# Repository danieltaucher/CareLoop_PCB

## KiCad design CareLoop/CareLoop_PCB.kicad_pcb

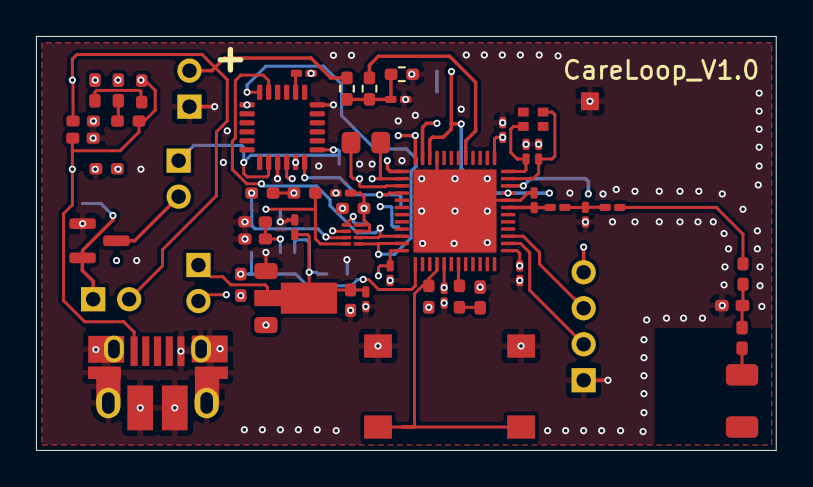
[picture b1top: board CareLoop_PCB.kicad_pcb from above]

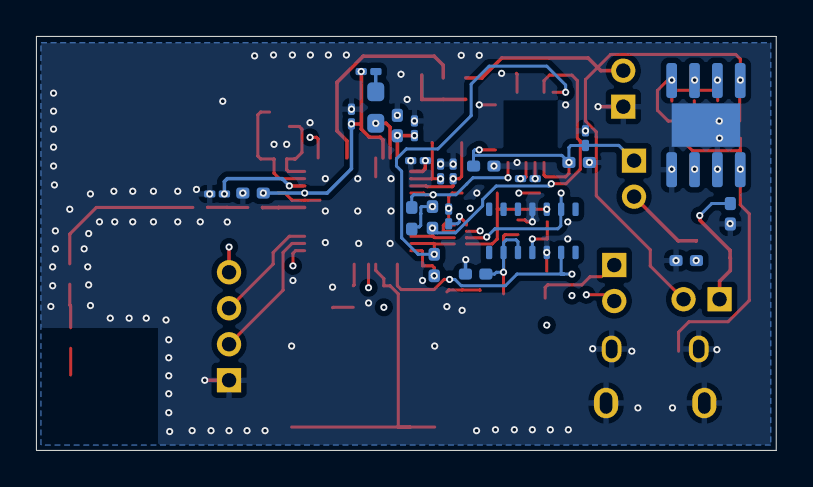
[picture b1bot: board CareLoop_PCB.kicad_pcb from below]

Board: 6 copper layers, 41.1 x 23.0 mm, 76 parts (23 on the bottom side), 43 nets.

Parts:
AE1: Antenna_Chip; Johanson_2450AT18x100
C1, C2: 12p; C_0201_0603Metric_Pad0.64x0.40mm_HandSolder
C3, C4: 4p; C_0201_0603Metric_Pad0.64x0.40mm_HandSolder
C5: 1p; C_0201_0603Metric_Pad0.64x0.40mm_HandSolder
C6: 1.2p; C_0201_0603Metric_Pad0.64x0.40mm_HandSolder
C7, C11, C22, C40, C42, C43: 1u; C_0402_1005Metric_Pad0.74x0.62mm_HandSolder
C8: 47n; C_0201_0603Metric_Pad0.64x0.40mm_HandSolder
C9, C26: 100p; C_0201_0603Metric_Pad0.64x0.40mm_HandSolder
C10, C12, C13, C13#2, C14, C15, C16, C20, C25, C27, C31, C32: 100n; C_0201_0603Metric_Pad0.64x0.40mm_HandSolder
C21, C23: 4.7u; C_0402_1005Metric_Pad0.74x0.62mm_HandSolder
C24, C41: 10u; C_0402_1005Metric_Pad0.74x0.62mm_HandSolder
C30, C30#2: 10n; C_0402_1005Metric_Pad0.74x0.62mm_HandSolder
C33: 2.2n; C_0201_0603Metric_Pad0.64x0.40mm_HandSolder
C50: C_Small; C_0402_1005Metric_Pad0.74x0.62mm_HandSolder
D3: LED_Small; LED_0402_1005Metric_Pad0.77x0.64mm_HandSolder
D40, D41: LED; LED_0402_1005Metric_Pad0.77x0.64mm_HandSolder
J1_Battery1: Conn_01x02_Pin; PinHeader_1x02_P2.00mm_Vertical
J1_DEBUG1: Conn_01x04_Pin; PinHeader_1x04_P2.00mm_Vertical
J2: USB_B_Micro; USB_Micro-B_Amphenol_10103594-0001LF_Horizontal
JP1_MAX30102, JP2_MPU1, JP2_MPU2: Jumper_2_Bridged; PinHeader_1x02_P2.00mm_Vertical
L1: 2.2n; L_0201_0603Metric_Pad0.64x0.40mm_HandSolder
L2: 4.7n; L_0201_0603Metric_Pad0.64x0.40mm_HandSolder
L5: 10u; L_0603_1608Metric_Pad1.05x0.95mm_HandSolder
L6: 15n; L_0201_0603Metric_Pad0.64x0.40mm_HandSolder
L50, L51: L_Small; L_0402_1005Metric_Pad0.77x0.64mm_HandSolder
R1, R20: 10k; R_0402_1005Metric_Pad0.72x0.64mm_HandSolder
R2, R3, R5, R22, R23: 4k7; R_0402_1005Metric_Pad0.72x0.64mm_HandSolder
R4: 800; R_0402_1005Metric_Pad0.72x0.64mm_HandSolder
R21: 200k; R_0402_1005Metric_Pad0.72x0.64mm_HandSolder
R40, R41: 1k; R_0402_1005Metric_Pad0.72x0.64mm_HandSolder
R42: 20k; R_0402_1005Metric_Pad0.72x0.64mm_HandSolder
R43: 120k; R_0402_1005Metric_Pad0.72x0.64mm_HandSolder
R44: 100; R_0402_1005Metric_Pad0.72x0.64mm_HandSolder
R45: 300k; R_0402_1005Metric_Pad0.72x0.64mm_HandSolder
Reset_SW1: SW_Push; SW_SPST_B3S-1000
U1: MCP1700x-180xxMB; SOT-89-3
U2: MAX30102; Maxim_OLGA-14_3.3x5.6mm_P0.8mm
U3: MPU-6050; InvenSense_QFN-24_4x4mm_P0.5mm
U4: MCP1700x-330xxMB; SOT-23
U5: TP4056-42-ESOP8; SOIC-8-1EP_3.9x4.9mm_P1.27mm_EP2.41x3.81mm
U6: nRF52840-QFXX; QFN-48-1EP_6x6mm_P0.4mm_EP4.6x4.6mm
U7: PCA9306; X2SON-8_1.4x1mm_P0.35mm
Y1: 32MHz; Oscillator_SMD_Abracon_ASCO-4Pin_1.6x1.2mm
Y2: 32.768kHz; Crystal_SMD_MicroCrystal_CM9V-T1A-2Pin_1.6x1.0mm_HandSolder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

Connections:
/Antenna/ANT: C50.1, L1.1
/Battery/BAT_Plus: C41.1, J1_Battery1.2, JP2_MPU1.2 (B), R43.2, U5.5 (BAT)
/Battery/CHRG: D41.1 (K), U5.7 (~CHRG)
/Battery/PROG: R42.1, U5.2 (PROG)
/Battery/STDBY: D40.1 (K), U5.6 (~STDBY)
/Battery/VBUS: C40.1, J2.1 (VBUS), R40.2, R41.2, U5.4 (V_{CC}), U5.8 (CE)
/Battery/VCC: C11.2, C12.2, C13.1, C14.2, C15.2, C16.2, C43.1, J1_DEBUG1.4, JP1_MAX30102.2 (B), JP2_MPU2.2 (B), R1.2, R2.1, R3.1, R5.1, R20.1, R21.2, U4.3 (VO), U6.12 (VDD), U6.17 (VDD), U6.25 (VDD), U6.37 (VDD), U6.48 (VDD)
/Battery/VIN_BATTERY: C42.1, JP2_MPU1.1 (A), U4.2 (VI)
/Battery/Vin_Battery_Status: R44.1, U6.41 (P0.28)
/MAX30102/MAX_INT: R20.2, U2.13 (~INT), U6.13 (P0.13)
/MAX30102/SCL: R3.2, U3.23 (SCL), U6.10 (P0.11), U7.6 (SCL2)
/MAX30102/SCL1: R22.2, U2.2 (SCL), U7.3 (SCL1)
/MAX30102/SDA: R2.2, U3.24 (SDA), U6.11 (P0.12), U7.5 (SDA2)
/MAX30102/SDA1: R23.2, U2.3 (SDA), U7.4 (SDA1)
/MAX30102/VCC_1.8V: C22.1, C23.1, R22.1, R23.1, U1.3 (VO), U2.11 (VDD), U7.2 (VREF1)
/MAX30102/VIN_MAX30102: C20.1, C21.1, C24.1, C25.1, JP1_MAX30102.1 (A), U1.2 (VI), U2.9 (VLED+), U2.10 (VLED+)
/MCU/ANT_PIN: C5.1, L2.2, U6.31 (ANT)
/MCU/DCC: L5.1, U6.47 (DCC)
/MCU/DEC1: C10.2, U6.1 (DEC1)
/MCU/DEC3: C9.2, U6.34 (DEC3)
/MCU/DEC4/DEC6: C7.1, C8.1, L6.2, U6.33 (DEC6), U6.46 (DEC4)
/MCU/INT_MPU: R5.2, U3.12 (INT), U6.4 (P0.04)
/MCU/Reset: R1.1, Reset_SW1.1, U6.16 (~RESET)
/MCU/SWDCLK: J1_DEBUG1.3, U6.27 (SWDCLK)
/MCU/SWDIO: J1_DEBUG1.2, U6.26 (SWDIO)
/MCU/Status_LED: R4.1, U6.19 (P0.20)
/MPU6050/CPOUT: C33.2, U3.20 (CPOUT)
/MPU6050/REGOUT: C32.1, U3.10 (REGOUT)
/MPU6050/VIN_MPU: C30.2, C30#2.2, C31.2, JP2_MPU2.1 (A), U3.8 (VLOGIC), U3.13 (VDD)
GND: C1.1, C2.1, C3.2, C4.2, C5.2, C6.2, C7.2, C8.2, C9.1, C10.1, C11.1, C12.1, C13.2, C13#2.1, C14.1, C15.1, C16.1, C20.2, C21.2, C22.2, C23.2, C24.2, C25.2, C26.1, C27.1, C30.1, C30#2.1, C31.1, C32.2, C33.1, C40.2, C41.2, C42.2, C43.2, D3.1 (K), J1_Battery1.1, J1_DEBUG1.1, J2.5 (GND), J2.6 (Shield), L51.2, R42.2, R45.1, Reset_SW1.2, U1.1 (GND), U2.4 (PGND), U2.12 (GND), U3.1 (CLKIN), U3.9 (AD0), U3.11 (FSYNC), U3.18 (GND), U4.1 (GND), U5.1 (TEMP), U5.3 (GND), U5.9 (EPAD), U6.32 (VSS_PA), U6.45 (VSS), U6.49 (VSS), U7.1 (GND)
unnamed: AE1.1 (FEED), L50.2
unnamed: C6.1, L1.2, L2.1
unnamed: C13#2.2, R43.1, R44.2, R45.2
unnamed: C50.2, L50.1, L51.1
unnamed: D3.2 (A), R4.2
unnamed: D40.2 (A), R40.1
unnamed: D41.2 (A), R41.1
unnamed: L5.2, L6.1
unnamed: C3.1, U6.2 (P0.00), Y2.2
unnamed: C4.1, U6.3 (P0.01), Y2.1
unnamed: C1.2, U6.35 (XC1), Y1.3
unnamed: C2.2, U6.36 (XC2), Y1.1
unnamed: C26.2, C27.2, R21.1, U7.7 (VREF2), U7.8 (EN)

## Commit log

2025-08-30 init
2025-09-16 updated version
2025-09-16 updated antenna version
2025-09-23 WP: update Schematics
2025-09-27 WP: Placement PCB Parts done
2025-10-12 WP: updatet version with routing
2025-10-14 WP: Version 1 done
2025-10-15 update routing
2025-10-15 updated vias
2025-10-16 PCB V1.0
2025-10-16 PCB update
2025-10-22 update PCB
2025-10-29 nordic review
2025-11-03 update Voltagedevider
2025-11-03 update PCB boarders
